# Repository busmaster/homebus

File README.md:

homebus
=======

home automation system

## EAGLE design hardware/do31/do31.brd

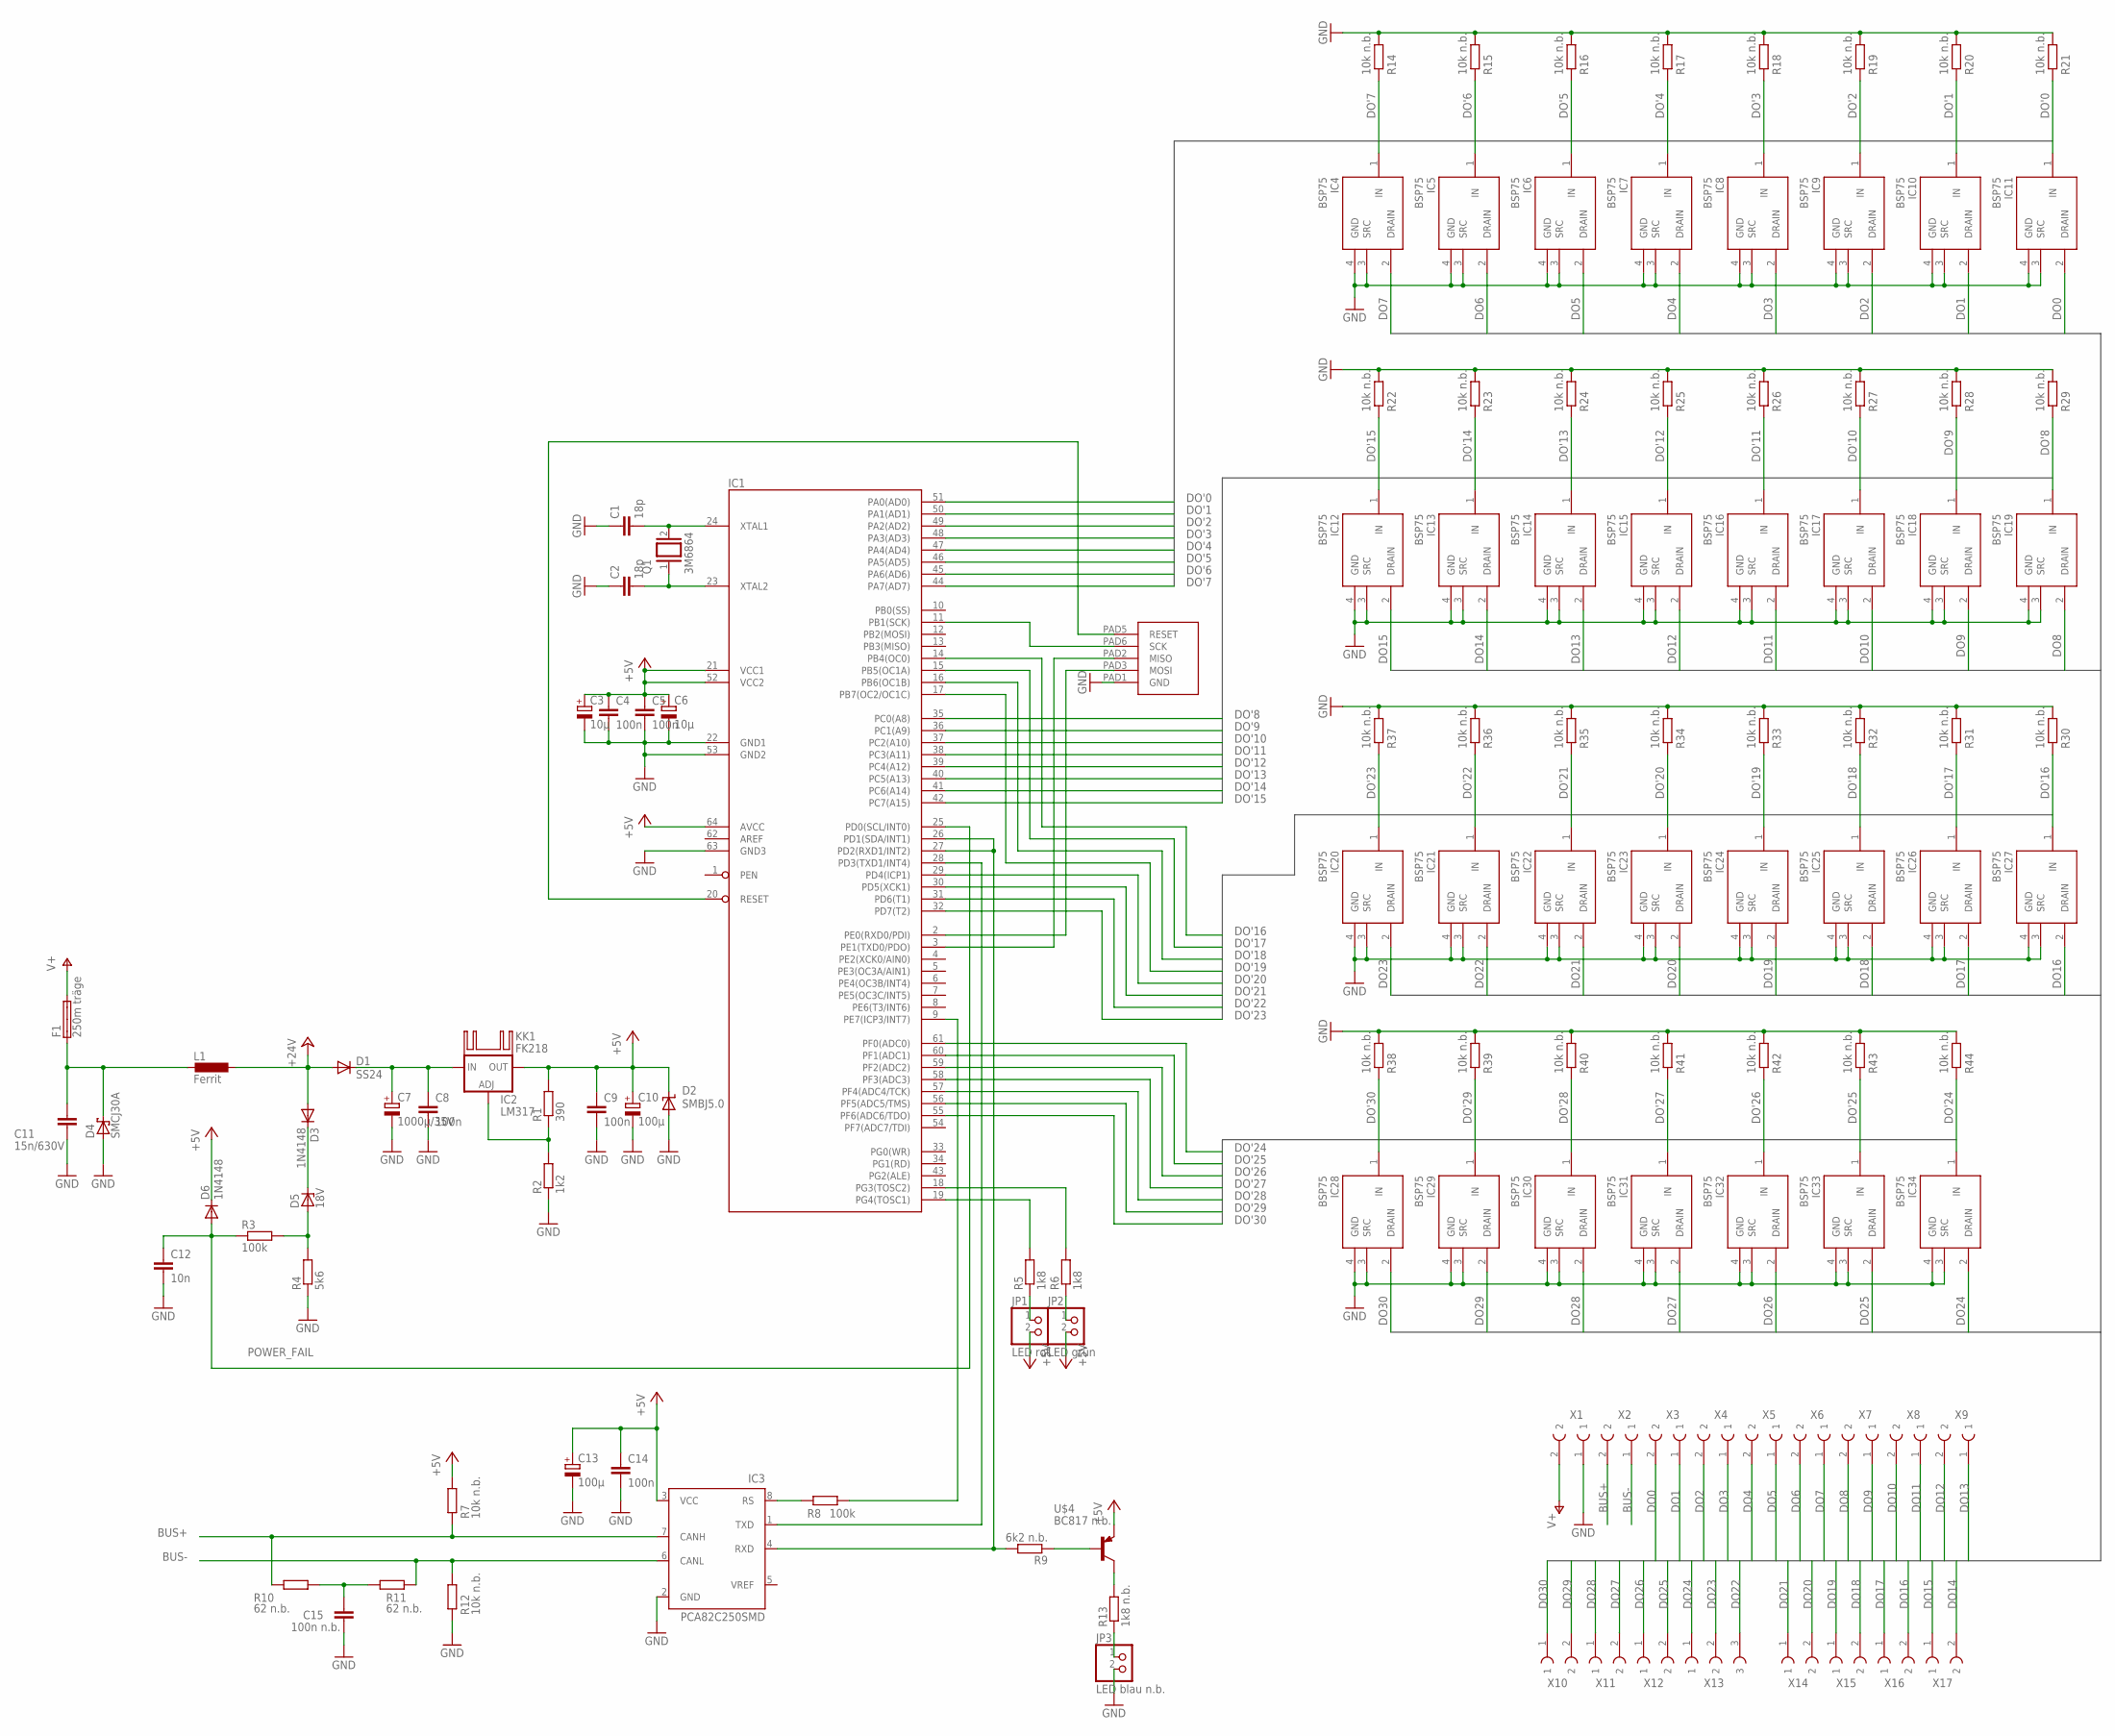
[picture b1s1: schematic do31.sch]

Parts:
C1, C2: 18p; C025-024X044
C3, C6: 10µ; E2-5
C4, C5, C8, C9, C14: 100n; C0603K
C7: 1000µ/35V; E5-13
C10, C13: 100µ; E2,5-5
C11: 15n/630V; C075-042X103
C12: 10n; C0603K
C15: 100n n.b.; C0603K
D1: SS24; SMB
D2: SMBJ5.0; SMBJ
D3, D6: 1N4148; D-2.5
D4: SMCJ30A; SMC
D5: 18V; ZDIO-2.5
F1: 250m träge; SHK20L
IC1: ATMEGA128; TQFP64
IC2: LM317; 317TS
IC3: PCA82C250SMD; SO8
IC4, IC5, IC6, IC7, IC8, IC9, IC10, IC11, IC12, IC13, IC14, IC15, IC16, IC17, IC18, IC19, IC20, IC21, IC22, IC23, IC24, IC25, IC26, IC27, IC28, IC29, IC30, IC31, IC32, IC33, IC34: BSP75; SOT223
JP1: LED rot; 1X02
JP2: LED grün; 1X02
JP3: LED blau n.b.; 1X02
KK1: FK218
L1: Ferrit; L1806
Q1: 3M6864; QS
R1: 390; R0603
R2: 1k2; R0603
R3, R8: 100k; R0603
R4: 5k6; R0603
R5, R6: 1k8; R0603
R7, R12, R14, R15, R16, R17, R18, R19, R20, R21, R22, R23, R24, R25, R26, R27, R28, R29, R30, R31, R32, R33, R34, R35, R36, R37, R38, R39, R40, R41, R42, R43, R44: 10k n.b.; R0603
R9: 6k2 n.b.; R0603
R10, R11: 62 n.b.; R0603
R13: 1k8 n.b.; R0603
U$1: ATMEL_ISP
U$4: BC817 n.b.; SOT323-BEC
X1, X2, X3, X4, X5, X6, X7, X8, X9, X10, X11, X12, X14, X15, X16, X17: AR-KLEMME_508_2POLPTR; W237-2E
X13: AR-KLEMME_508_3POLPTR; W237-3E

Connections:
+5V: C3.+, C4.1, C5.1, C6.+, C9.1, C10.+, C13.+, C14.1, D2.C, D6.C, IC1.21 (VCC1), IC1.52 (VCC2), IC1.64 (AVCC), IC2.2 (OUT), IC3.3 (VCC), JP1.2, JP2.2, R1.2, R7.1, U$4.E
+24V: D1.A, D3.A, L1.1
/RESET: IC1.20 (RESET), U$1.PAD5 (RESET)
AREF: IC1.62 (AREF)
BUS+: IC3.7 (CANH), R7.2, R10.2, X2.2
BUS-: IC3.6 (CANL), R11.1, R12.1, X2.1
DO0: IC11.2 (DRAIN), X3.2
DO1: IC10.2 (DRAIN), X3.1
DO2: IC9.2 (DRAIN), X4.2
DO3: IC8.2 (DRAIN), X4.1
DO4: IC7.2 (DRAIN), X5.2
DO5: IC6.2 (DRAIN), X5.1
DO6: IC5.2 (DRAIN), X6.2
DO7: IC4.2 (DRAIN), X6.1
DO8: IC19.2 (DRAIN), X7.2
DO9: IC18.2 (DRAIN), X7.1
DO10: IC17.2 (DRAIN), X8.2
DO11: IC16.2 (DRAIN), X8.1
DO12: IC15.2 (DRAIN), X9.2
DO13: IC14.2 (DRAIN), X9.1
DO14: IC13.2 (DRAIN), X17.2
DO15: IC12.2 (DRAIN), X17.1
DO16: IC27.2 (DRAIN), X16.2
DO17: IC26.2 (DRAIN), X16.1
DO18: IC25.2 (DRAIN), X15.2
DO19: IC24.2 (DRAIN), X15.1
DO20: IC23.2 (DRAIN), X14.2
DO21: IC22.2 (DRAIN), X14.1
DO22: IC21.2 (DRAIN), X13.3
DO23: IC20.2 (DRAIN), X13.2
DO24: IC34.2 (DRAIN), X13.1
DO25: IC33.2 (DRAIN), X12.2
DO26: IC32.2 (DRAIN), X12.1
DO27: IC31.2 (DRAIN), X11.2
DO28: IC30.2 (DRAIN), X11.1
DO29: IC29.2 (DRAIN), X10.2
DO30: IC28.2 (DRAIN), X10.1
DO'0: IC1.51 (PA0(AD0)), IC11.1 (IN), R21.2
DO'1: IC1.50 (PA1(AD1)), IC10.1 (IN), R20.2
DO'2: IC1.49 (PA2(AD2)), IC9.1 (IN), R19.2
DO'3: IC1.48 (PA3(AD3)), IC8.1 (IN), R18.2
DO'4: IC1.47 (PA4(AD4)), IC7.1 (IN), R17.2
DO'5: IC1.46 (PA5(AD5)), IC6.1 (IN), R16.2
DO'6: IC1.45 (PA6(AD6)), IC5.1 (IN), R15.2
DO'7: IC1.44 (PA7(AD7)), IC4.1 (IN), R14.2
DO'8: IC1.35 (PC0(A8)), IC19.1 (IN), R29.2
DO'9: IC1.36 (PC1(A9)), IC18.1 (IN), R28.2
DO'10: IC1.37 (PC2(A10)), IC17.1 (IN), R27.2
DO'11: IC1.38 (PC3(A11)), IC16.1 (IN), R26.2
DO'12: IC1.39 (PC4(A12)), IC15.1 (IN), R25.2
DO'13: IC1.40 (PC5(A13)), IC14.1 (IN), R24.2
DO'14: IC1.41 (PC6(A14)), IC13.1 (IN), R23.2
DO'15: IC1.42 (PC7(A15)), IC12.1 (IN), R22.2
DO'16: IC1.14 (PB4(OC0)), IC27.1 (IN), R30.2
DO'17: IC1.15 (PB5(OC1A)), IC26.1 (IN), R31.2
DO'18: IC1.16 (PB6(OC1B)), IC25.1 (IN), R32.2
DO'19: IC1.17 (PB7(OC2/OC1C)), IC24.1 (IN), R33.2
DO'20: IC1.29 (PD4(ICP1)), IC23.1 (IN), R34.2
DO'21: IC1.30 (PD5(XCK1)), IC22.1 (IN), R35.2
DO'22: IC1.31 (PD6(T1)), IC21.1 (IN), R36.2
DO'23: IC1.32 (PD7(T2)), IC20.1 (IN), R37.2
DO'24: IC1.61 (PF0(ADC0)), IC34.1 (IN), R44.2
DO'25: IC1.60 (PF1(ADC1)), IC33.1 (IN), R43.2
DO'26: IC1.59 (PF2(ADC2)), IC32.1 (IN), R42.2
DO'27: IC1.58 (PF3(ADC3)), IC31.1 (IN), R41.2
DO'28: IC1.57 (PF4(ADC4/TCK)), IC30.1 (IN), R40.2
DO'29: IC1.56 (PF5(ADC5/TMS)), IC29.1 (IN), R39.2
DO'30: IC1.55 (PF6(ADC6/TDO)), IC28.1 (IN), R38.2
GND: C1.1, C2.1, C3.-, C4.2, C5.2, C6.-, C7.-, C8.2, C9.2, C10.-, C11.2, C12.2, C13.-, C14.2, C15.1, D2.A, D4.A, IC1.22 (GND1), IC1.53 (GND2), IC1.63 (GND3), IC3.2 (GND), IC4.3 (SRC), IC4.4 (GND), IC5.3 (SRC), IC5.4 (GND), IC6.3 (SRC), IC6.4 (GND), IC7.3 (SRC), IC7.4 (GND), IC8.3 (SRC), IC8.4 (GND), IC9.3 (SRC), IC9.4 (GND), IC10.3 (SRC), IC10.4 (GND), IC11.3 (SRC), IC11.4 (GND), IC12.3 (SRC), IC12.4 (GND), IC13.3 (SRC), IC13.4 (GND), IC14.3 (SRC), IC14.4 (GND), IC15.3 (SRC), IC15.4 (GND), IC16.3 (SRC), IC16.4 (GND), IC17.3 (SRC), IC17.4 (GND), IC18.3 (SRC), IC18.4 (GND), IC19.3 (SRC), IC19.4 (GND), IC20.3 (SRC), IC20.4 (GND), IC21.3 (SRC), IC21.4 (GND), IC22.3 (SRC), IC22.4 (GND), IC23.3 (SRC), IC23.4 (GND), IC24.3 (SRC), IC24.4 (GND), IC25.3 (SRC), IC25.4 (GND), IC26.3 (SRC), IC26.4 (GND), IC27.3 (SRC), IC27.4 (GND), IC28.3 (SRC), IC28.4 (GND), IC29.3 (SRC), IC29.4 (GND), IC30.3 (SRC), IC30.4 (GND), IC31.3 (SRC), IC31.4 (GND), IC32.3 (SRC), IC32.4 (GND), IC33.3 (SRC), IC33.4 (GND), IC34.3 (SRC), IC34.4 (GND), JP3.2, R2.1, R4.1, R12.2, R14.1, R15.1, R16.1, R17.1, R18.1, R19.1, R20.1, R21.1, R22.1, R23.1, R24.1, R25.1, R26.1, R27.1, R28.1, R29.1, R30.1, R31.1, R32.1, R33.1, R34.1, R35.1, R36.1, R37.1, R38.1, R39.1, R40.1, R41.1, R42.1, R43.1, R44.1, U$1.PAD1 (GND), X1.1
MISO: IC1.3 (PE1(TXD0/PDO)), U$1.PAD2 (MISO)
MOSI: IC1.2 (PE0(RXD0/PDI)), U$1.PAD3 (MOSI)
unnamed: C11.1, D4.C, F1.1A, L1.2
unnamed: D3.C, D5.C
unnamed: D5.A, R3.2, R4.2
unnamed: C1.2, IC1.24 (XTAL1), Q1.2
unnamed: C2.2, IC1.23 (XTAL2), Q1.1
unnamed: IC3.8 (RS), R8.2
unnamed: IC1.9 (PE7(ICP3/INT7)), R8.1
unnamed: IC2.1 (ADJ), R1.1, R2.2
unnamed: R9.1, U$4.B
unnamed: R13.2, U$4.C
unnamed: C7.+, C8.1, D1.C, IC2.3 (IN)
unnamed: JP3.1, R13.1
unnamed: C15.2, R10.1, R11.2
unnamed: JP1.1, R5.1
unnamed: JP2.1, R6.1
unnamed: IC1.19 (PG4(TOSC1)), R5.2
unnamed: IC1.18 (PG3(TOSC2)), R6.2
POWER_FAIL: C12.1, D6.A, IC1.25 (PD0(SCL/INT0)), R3.1
RXD: IC1.26 (PD1(SDA/INT1)), IC1.27 (PD2(RXD1/INT2)), IC3.4 (RXD), R9.2
SCK: IC1.11 (PB1(SCK)), U$1.PAD6 (SCK)
TXD: IC1.28 (PD3(TXD1/INT4)), IC3.1 (TXD)
V+: F1.2A, X1.2

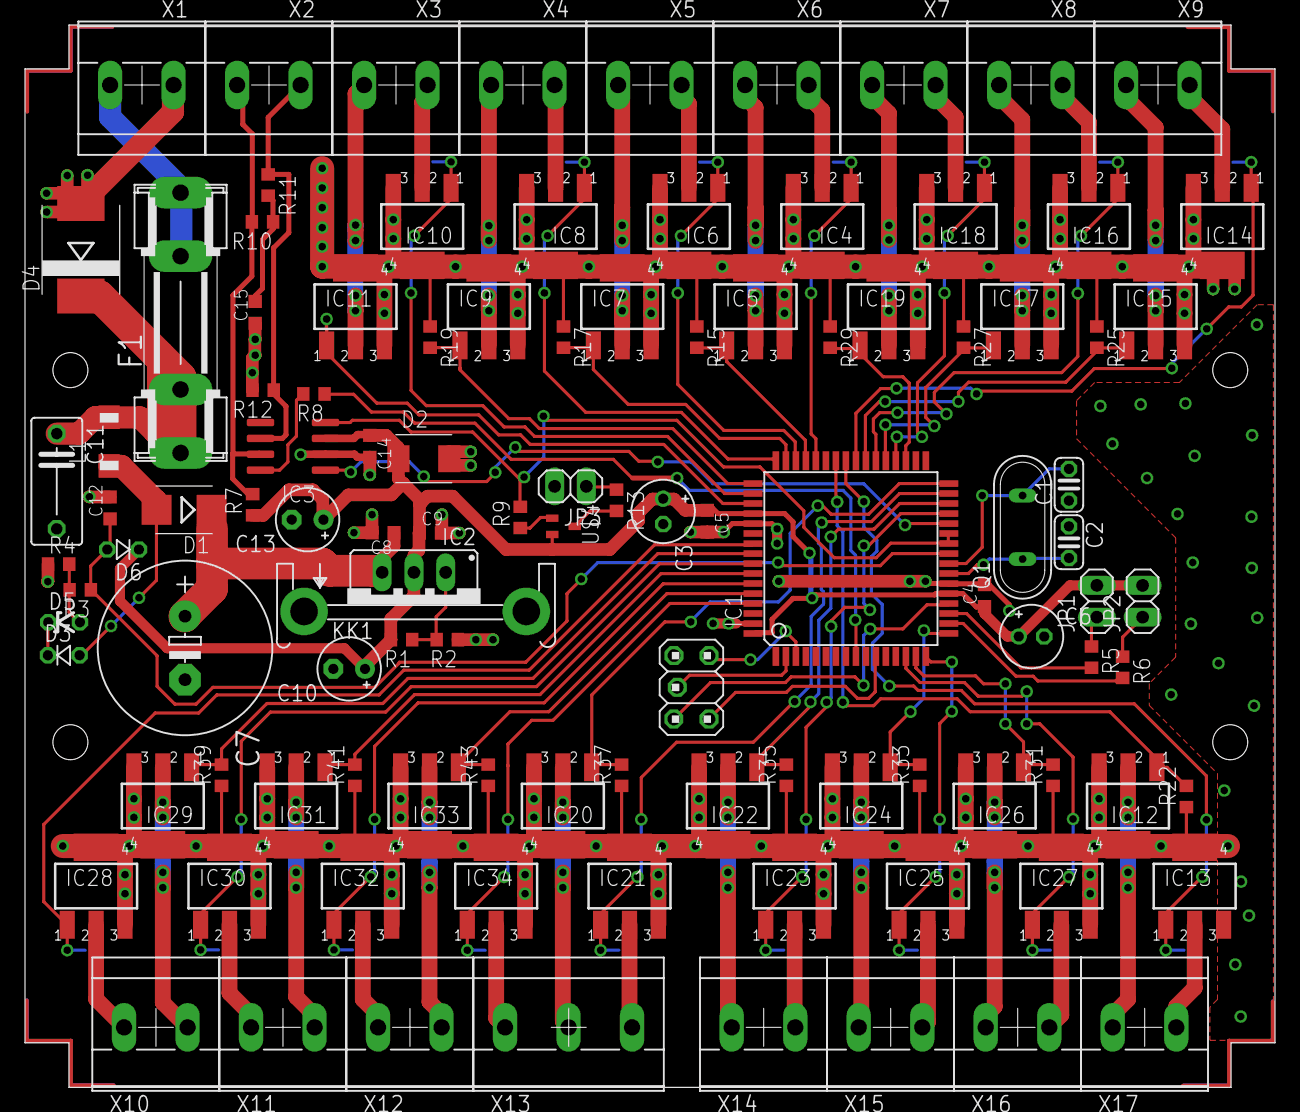
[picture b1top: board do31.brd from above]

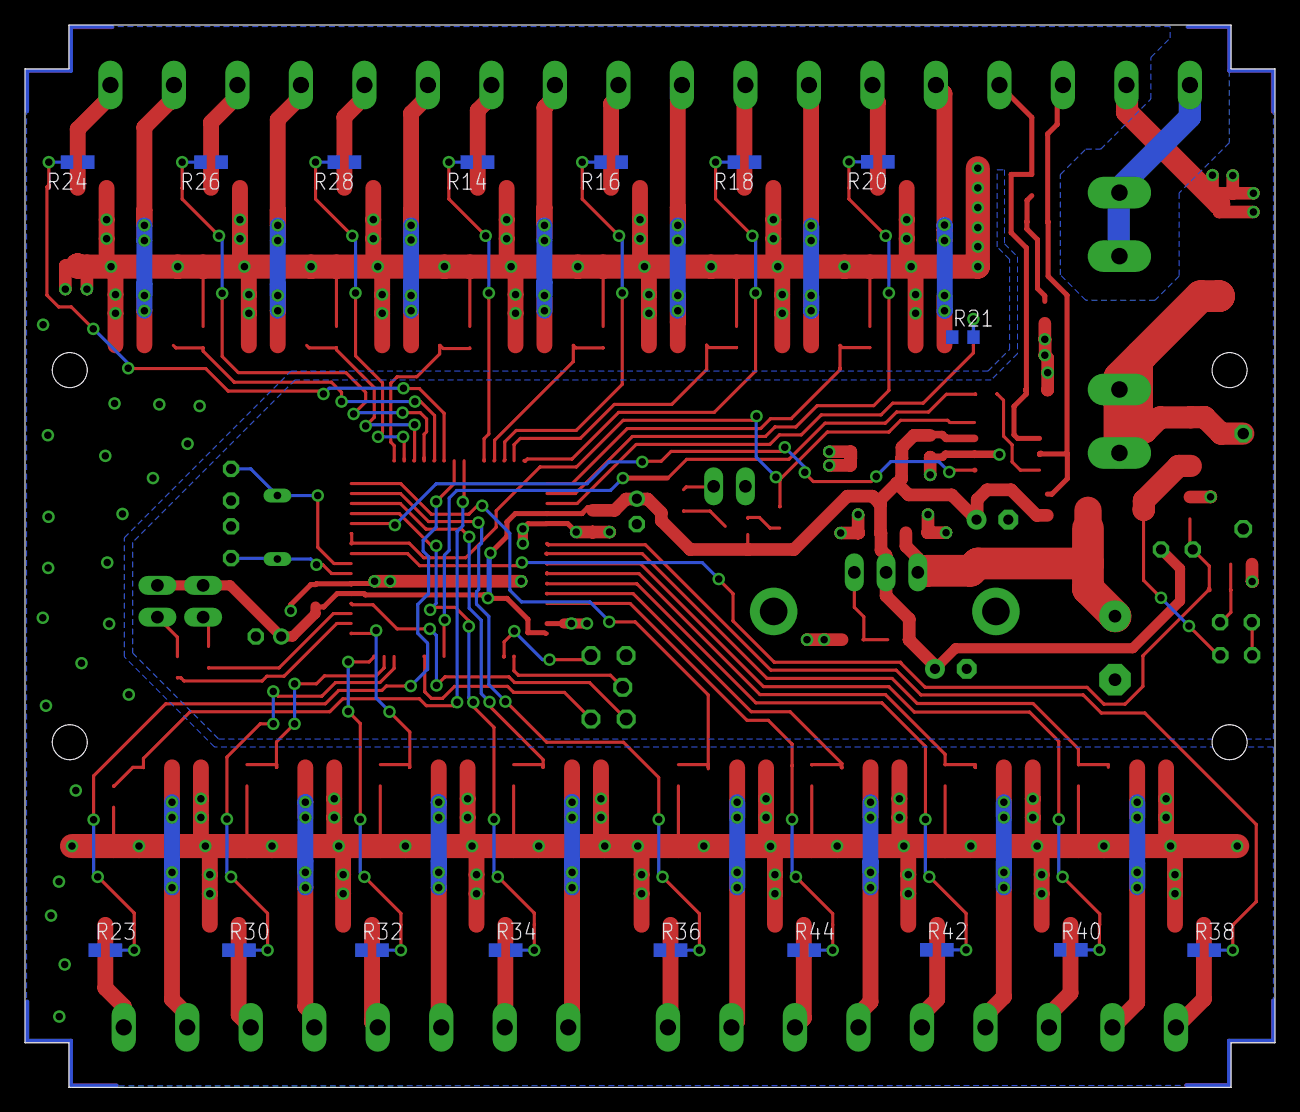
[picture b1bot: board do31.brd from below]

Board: 2 copper layers, 100.0 x 85.0 mm, 126 parts (17 on the bottom side), 92 nets.

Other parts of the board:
U$3: GEHÄUSE_MR6

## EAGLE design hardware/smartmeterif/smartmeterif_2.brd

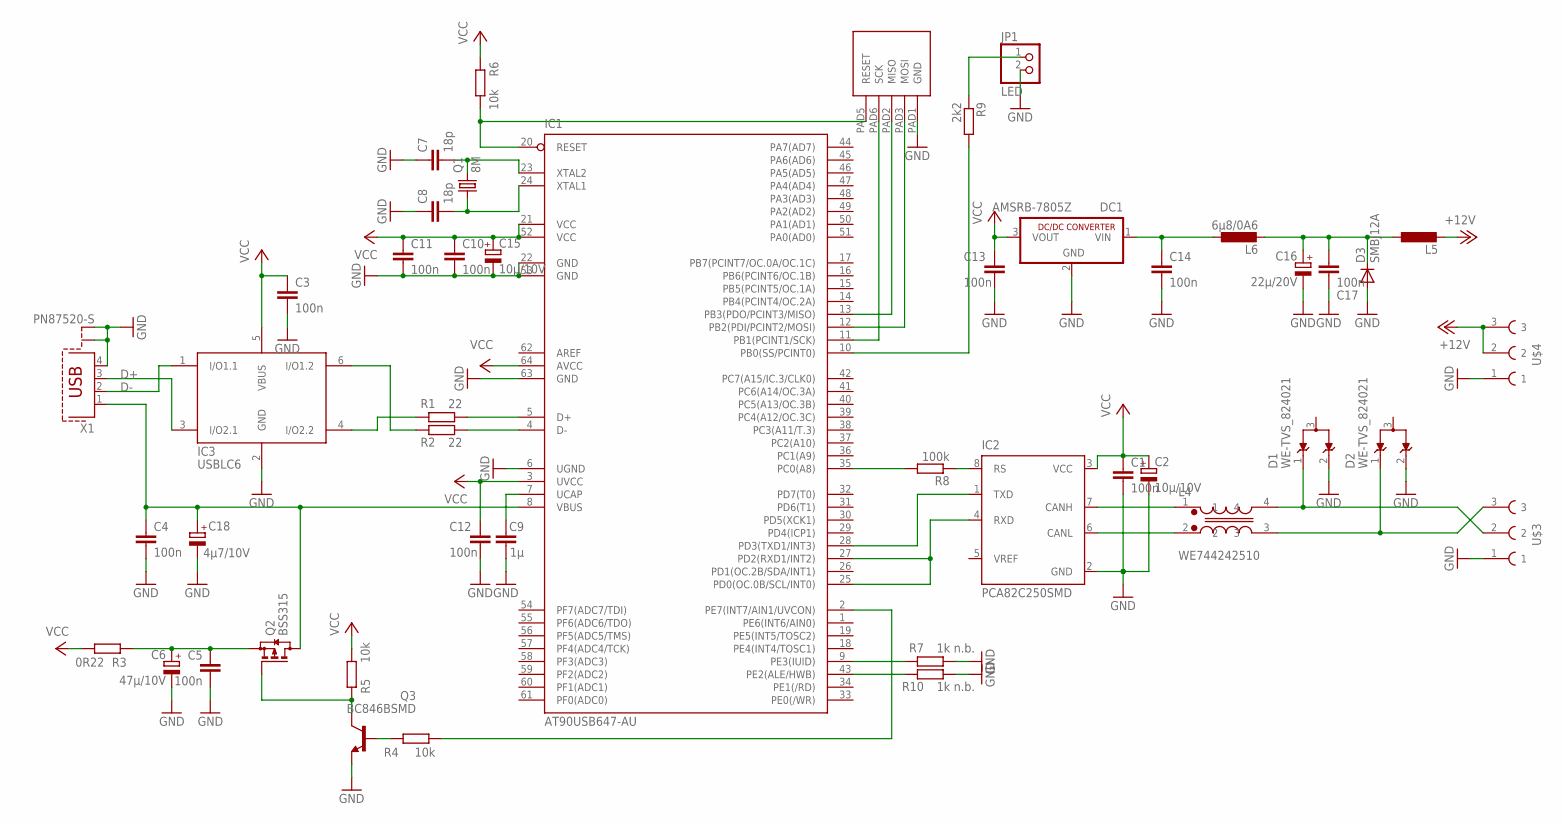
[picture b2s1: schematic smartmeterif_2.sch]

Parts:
C1, C3, C4, C5, C10, C11, C12, C13, C14, C17: 100n; C0603
C2, C15: 10µ/10V; A/3216-18W
C6: 47µ/10V; SMC_C
C7, C8: 18p; C0603
C9: 1µ; C1210K
C16: 22µ/20V; SMC_C
C18: 4µ7/10V; SMC_A
D1, D2: WE-TVS_824021; WE-TVS_SOT23-3L
D3: SMBJ12A; SMB
DC1: AMSRB-7805Z; SIP3
IC1: AT90USB647-AU; TQFP64
IC2: PCA82C250SMD; SO8
IC3: USBLC6; SOT23-6L
JP1: LED; 1X02
L4: WE744242510; WE-SLM
L5: L-EUL1806; L1806
L6: 6µ8/0A6; L1812
Q1: 8M; SM49
Q2: BSS315; SOT23
Q3: BC846BSMD; SOT23
R1, R2: 22; R0603
R3: 0R22; R0603
R4, R5, R6: 10k; R0603
R7, R10: 1k n.b.; R0603
R8: 100k; R0603
R9: 2k2; R0603
U$2: ATMEL_ISP
U$3, U$4: MKDSO_2.5/3_L; PHOENIX_MKDSO_2.5/3_L
X1: PN87520-S

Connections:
+12V: L5.2, U$4.2, U$4.3
.D+: IC3.4 (I/O2.2), R1.1
.D-: IC3.6 (I/O1.2), R2.1
B+: D1.1, L4.4, U$3.2
B-: D2.1, L4.3, U$3.3
D+: IC3.3 (I/O2.1), X1.3
D-: IC3.1 (I/O1.1), X1.2
GND: C1.2, C2.-, C3.2, C4.2, C5.2, C6.-, C7.1, C8.1, C9.1, C10.2, C11.2, C12.2, C13.2, C14.2, C15.-, C16.-, C17.2, C18.-, D1.2, D2.2, D3.A, DC1.2 (GND), IC1.6 (UGND), IC1.22 (GND), IC1.53 (GND), IC1.63 (GND), IC2.2 (GND), IC3.2 (GND), JP1.2, Q3.2 (E), R7.2, R10.2, U$2.PAD1 (GND), U$3.1, U$4.1, X1.4, X1.S1, X1.S2
unnamed: IC1.5 (D+), R1.2
unnamed: IC1.4 (D-), R2.2
unnamed: C4.1, C18.+, IC1.8 (VBUS), Q2.3 (D), X1.1
unnamed: C5.1, C6.+, Q2.2 (S), R3.1
unnamed: IC1.2 (PE7(INT7/AIN1/UVCON)), R4.2
unnamed: IC2.7 (CANH), L4.1
unnamed: Q2.1 (G), Q3.3 (C), R5.1
unnamed: Q3.1 (B), R4.1
unnamed: IC1.10 (PB0(SS/PCINT0)), R9.2
unnamed: JP1.1, R9.1
unnamed: IC1.35 (PC0(A8)), R8.2
unnamed: IC1.28 (PD3(TXD1/INT3)), IC2.1 (TXD)
unnamed: IC2.6 (CANL), L4.2
unnamed: IC1.25 (PD0(OC.0B/SCL/INT0)), IC1.27 (PD2(RXD1/INT2)), IC2.4 (RXD)
unnamed: IC1.43 (PE2(ALE/HWB)), R10.1
unnamed: IC1.20 (RESET), R6.2, U$2.PAD5 (RESET)
unnamed: IC1.11 (PB1(PCINT1/SCK)), U$2.PAD6 (SCK)
unnamed: IC1.12 (PB2(PDI/PCINT2/MOSI)), U$2.PAD3 (MOSI)
unnamed: IC1.13 (PB3(PDO/PCINT3/MISO)), U$2.PAD2 (MISO)
unnamed: C7.2, IC1.23 (XTAL2), Q1.2
unnamed: C8.2, IC1.24 (XTAL1), Q1.1
unnamed: C9.2, IC1.7 (UCAP)
unnamed: IC2.8 (RS), R8.1
unnamed: C16.+, C17.1, D3.C, L5.1, L6.2
unnamed: C14.1, DC1.1 (VIN), L6.1
unnamed: IC1.9 (PE3(IUID)), R7.1
VCC: C1.1, C2.+, C3.1, C10.1, C11.1, C12.1, C13.1, C15.+, DC1.3 (VOUT), IC1.3 (UVCC), IC1.21 (VCC), IC1.52 (VCC), IC1.64 (AVCC), IC2.3 (VCC), IC3.5 (VBUS), R3.2, R5.2, R6.1

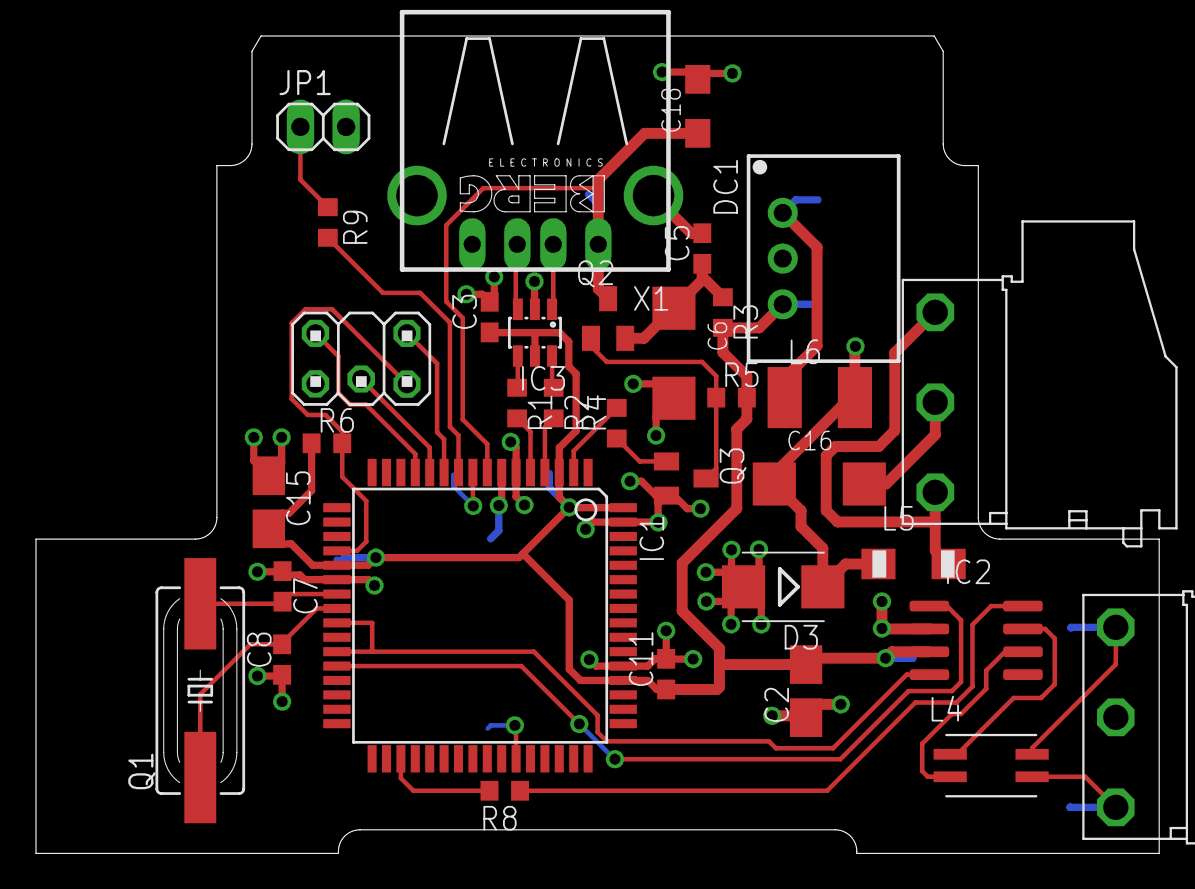
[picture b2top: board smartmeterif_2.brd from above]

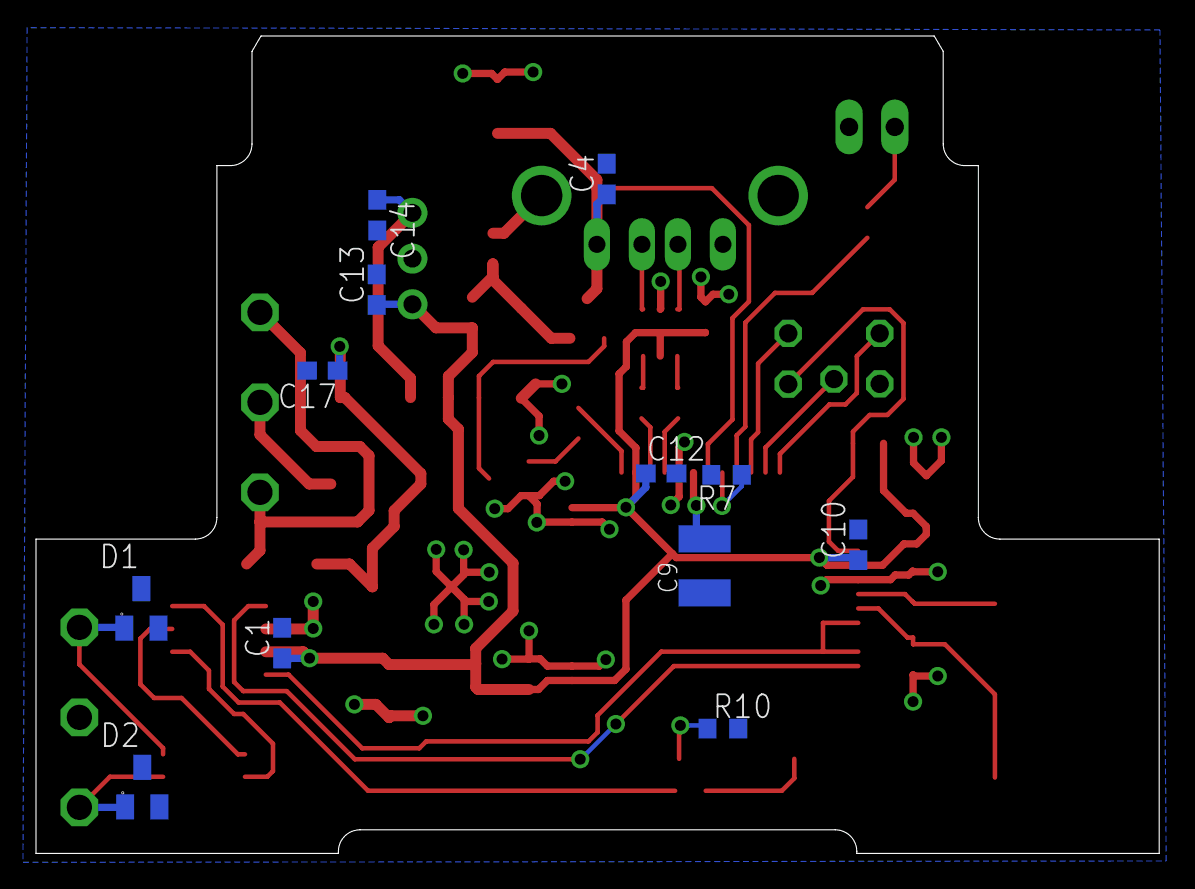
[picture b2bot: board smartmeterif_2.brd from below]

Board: 2 copper layers, 62.4 x 45.4 mm, 47 parts (12 on the bottom side), 35 nets.

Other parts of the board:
U$5: GEHÄUSE_PHOENIX_BC_17.8_REDUCED_REDUCED

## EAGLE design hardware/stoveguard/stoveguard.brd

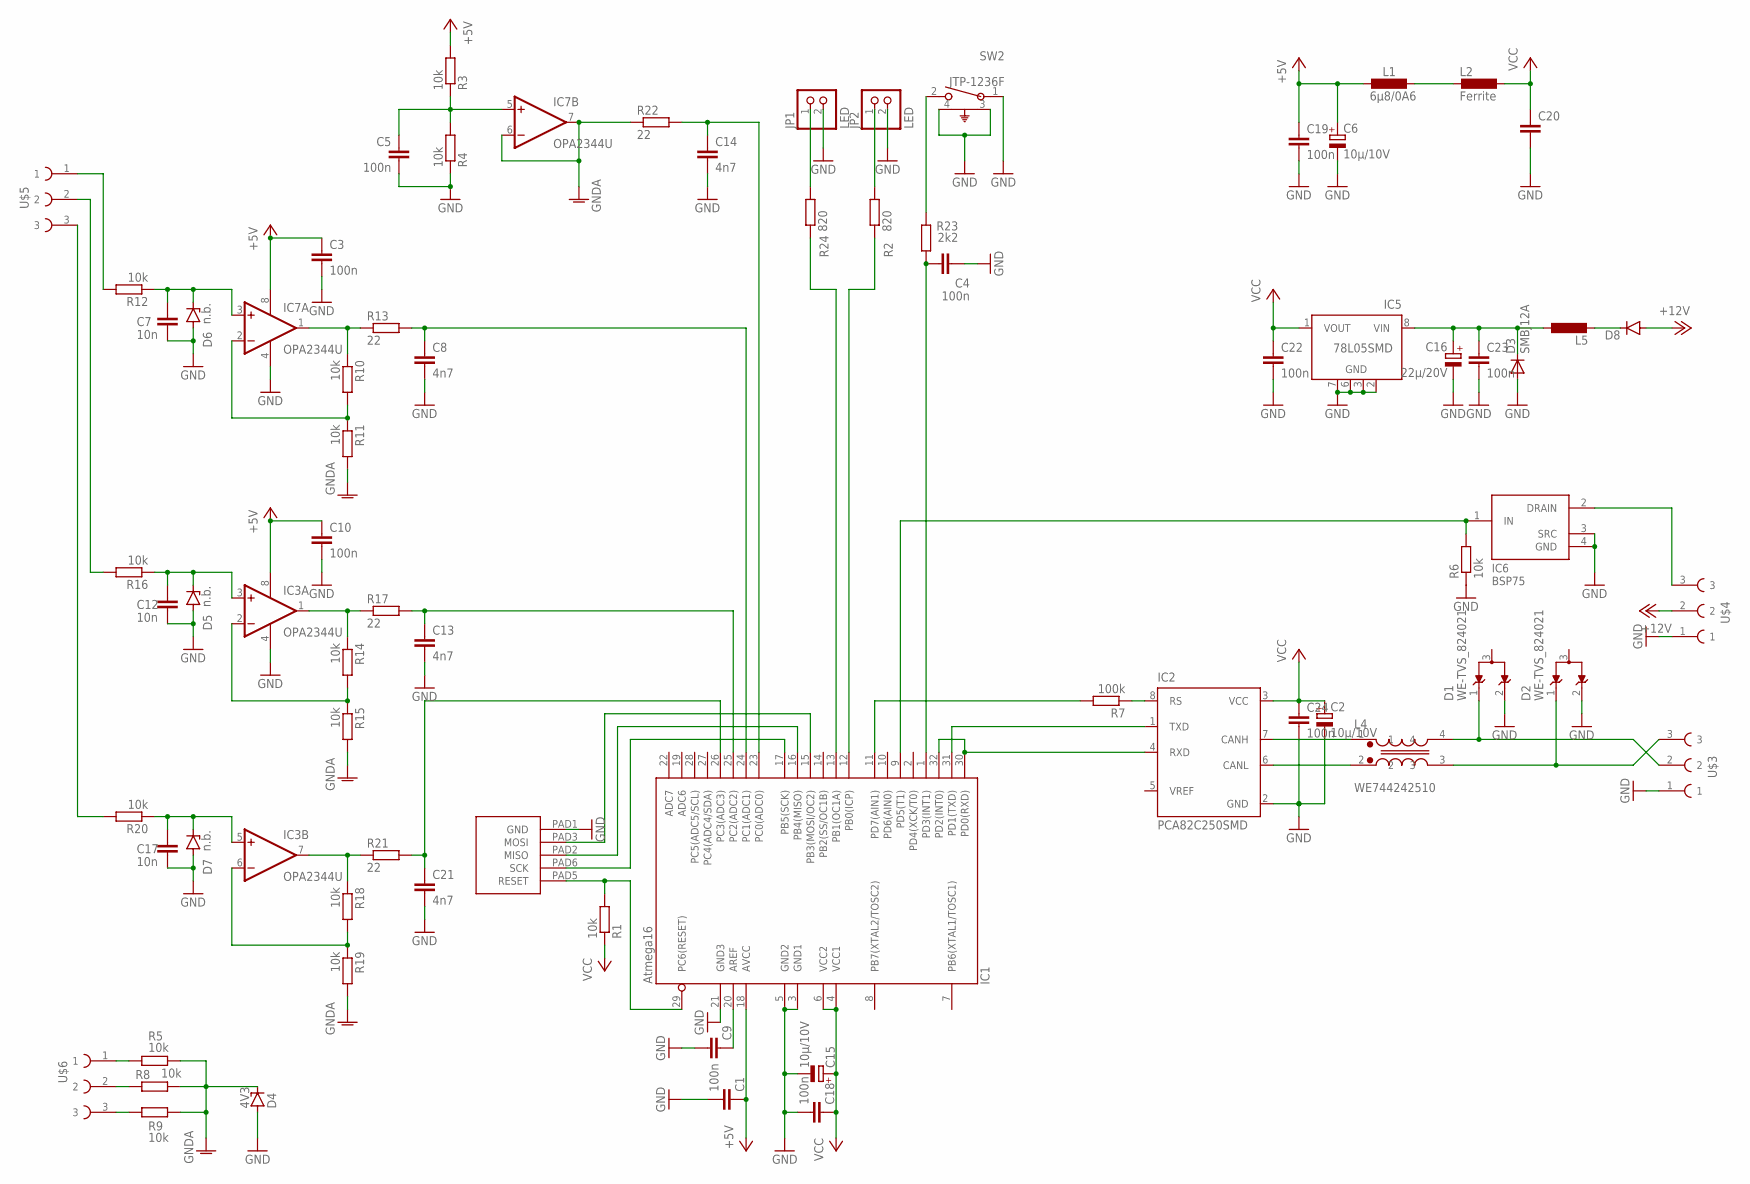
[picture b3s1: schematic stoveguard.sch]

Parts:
C1, C3, C4, C5, C10, C18, C19, C22, C23, C24: 100n; C0603
C2, C6, C15: 10µ/10V; A/3216-18W
C7, C12, C17: 10n; C0603
C8, C13, C14, C21: 4n7; C0603
C9: CC1206; C1206
C16: 22µ/20V; SMC_C
C20: CC0603; C0603
D1, D2: WE-TVS_824021; WE-TVS_SOT23-3L
D3: SMBJ12A; SMB
D4: 4V3; SOD80C
D5, D6, D7: n.b.; SOD80C
D8: DIODE-MINIMELF; MINIMELF
IC1: Atmega16; TQFP32-08
IC2: PCA82C250SMD; SO8
IC3, IC7: OPA2344U; SO08
IC5: 78L05SMD; SO08
IC6: BSP75; SOT223
JP1, JP2: LED; 1X02
L1: 6µ8/0A6; L1812
L2: Ferrite; L1806
L4: WE744242510; WE-SLM
L5: L-EUL1806; L1806
R1, R3, R4, R5, R6, R8, R9, R10, R11, R12, R14, R15, R16, R18, R19, R20: 10k; R0603
R2, R24: 820; R0603
R7: 100k; R0603
R13, R17, R21, R22: 22; R0603
R23: 2k2; R0603
SW2: JTP-1236F; SW2_1825027-E
U$2: ATMEL_ISP
U$3, U$4: MKDSO_2.5/3_L; PHOENIX_MKDSO_2.5/3_L
U$5, U$6: MKDSO_2.5/3_R; PHOENIX_MKDSO_2.5/3_R

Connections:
+5V: C1.1, C3.1, C6.+, C10.1, C19.1, IC1.18 (AVCC), IC3.8 (V+), IC7.8 (V+), L1.2, R3.2
+12V: D8.A, U$4.2
B+: D1.1, L4.4, U$3.2
B-: D2.1, L4.3, U$3.3
GND: C1.2, C2.-, C3.2, C4.1, C5.2, C6.-, C7.2, C8.2, C9.2, C10.2, C12.2, C13.2, C14.2, C15.-, C16.-, C17.2, C18.2, C19.2, C20.2, C21.2, C22.2, C23.2, C24.2, D1.2, D2.2, D3.A, D4.A, D5.A, D6.A, D7.A, IC1.3 (GND1), IC1.5 (GND2), IC1.21 (GND3), IC2.2 (GND), IC3.4 (V-), IC5.2 (GND), IC5.3 (GND), IC5.6 (GND), IC5.7 (GND), IC6.3 (SRC), IC6.4 (GND), IC7.4 (V-), JP1.2, JP2.2, R4.1, R6.1, SW2.1, SW2.3, SW2.4, U$2.PAD1 (GND), U$3.1, U$4.1
GNDA: D4.C, IC7.6 (-IN), IC7.7 (OUT), R5.1, R8.1, R9.1, R11.2, R15.2, R19.2, R22.1
unnamed: L1.1, L2.2
unnamed: IC6.2 (DRAIN), U$4.3
unnamed: C9.1, IC1.20 (AREF)
unnamed: IC1.15 (PB3(MOSI/OC2)), U$2.PAD3 (MOSI)
unnamed: IC1.16 (PB4(MISO)), U$2.PAD2 (MISO)
unnamed: IC1.17 (PB5(SCK)), U$2.PAD6 (SCK)
unnamed: IC1.9 (PD5(T1)), IC6.1 (IN), R6.2
unnamed: R5.2, U$6.1
unnamed: C5.1, IC7.5 (+IN), R3.1, R4.2
unnamed: IC2.7 (CANH), L4.1
unnamed: R8.2, U$6.2
unnamed: R9.2, U$6.3
unnamed: JP1.1, R24.2
unnamed: IC1.12 (PB0(ICP)), R2.1
unnamed: IC1.11 (PD7(AIN1)), R7.2
unnamed: IC1.31 (PD1(TXD)), IC2.1 (TXD)
unnamed: IC2.6 (CANL), L4.2
unnamed: IC1.30 (PD0(RXD)), IC1.32 (PD2(INT0)), IC2.4 (RXD)
unnamed: R12.2, U$5.1
unnamed: IC1.29 (PC6(RESET)), R1.2, U$2.PAD5 (RESET)
unnamed: C7.1, D6.C, IC7.3 (+IN), R12.1
unnamed: IC7.2 (-IN), R10.2, R11.1
unnamed: IC7.1 (OUT), R10.1, R13.1
unnamed: C4.2, IC1.1 (PD3(INT1)), R23.2
unnamed: R23.1, SW2.2
unnamed: C8.1, IC1.24 (PC1(ADC1)), R13.2
unnamed: IC2.8 (RS), R7.1
unnamed: C16.+, C23.1, D3.C, IC5.8 (VIN), L5.1
unnamed: C12.1, D5.C, IC3.3 (+IN), R16.1
unnamed: IC3.2 (-IN), R14.2, R15.1
unnamed: IC3.1 (OUT), R14.1, R17.1
unnamed: C13.1, IC1.25 (PC2(ADC2)), R17.2
unnamed: R16.2, U$5.2
unnamed: C17.1, D7.C, IC3.5 (+IN), R20.1
unnamed: IC3.6 (-IN), R18.2, R19.1
unnamed: IC3.7 (OUT), R18.1, R21.1
unnamed: C21.1, IC1.26 (PC3(ADC3)), R21.2
unnamed: R20.2, U$5.3
unnamed: C14.1, IC1.23 (PC0(ADC0)), R22.2
unnamed: D8.C, L5.2
unnamed: IC1.13 (PB1(OC1A)), R24.1
unnamed: JP2.1, R2.2
VCC: C2.+, C15.+, C18.1, C20.1, C22.1, C24.1, IC1.4 (VCC1), IC1.6 (VCC2), IC2.3 (VCC), IC5.1 (VOUT), L2.1, R1.1

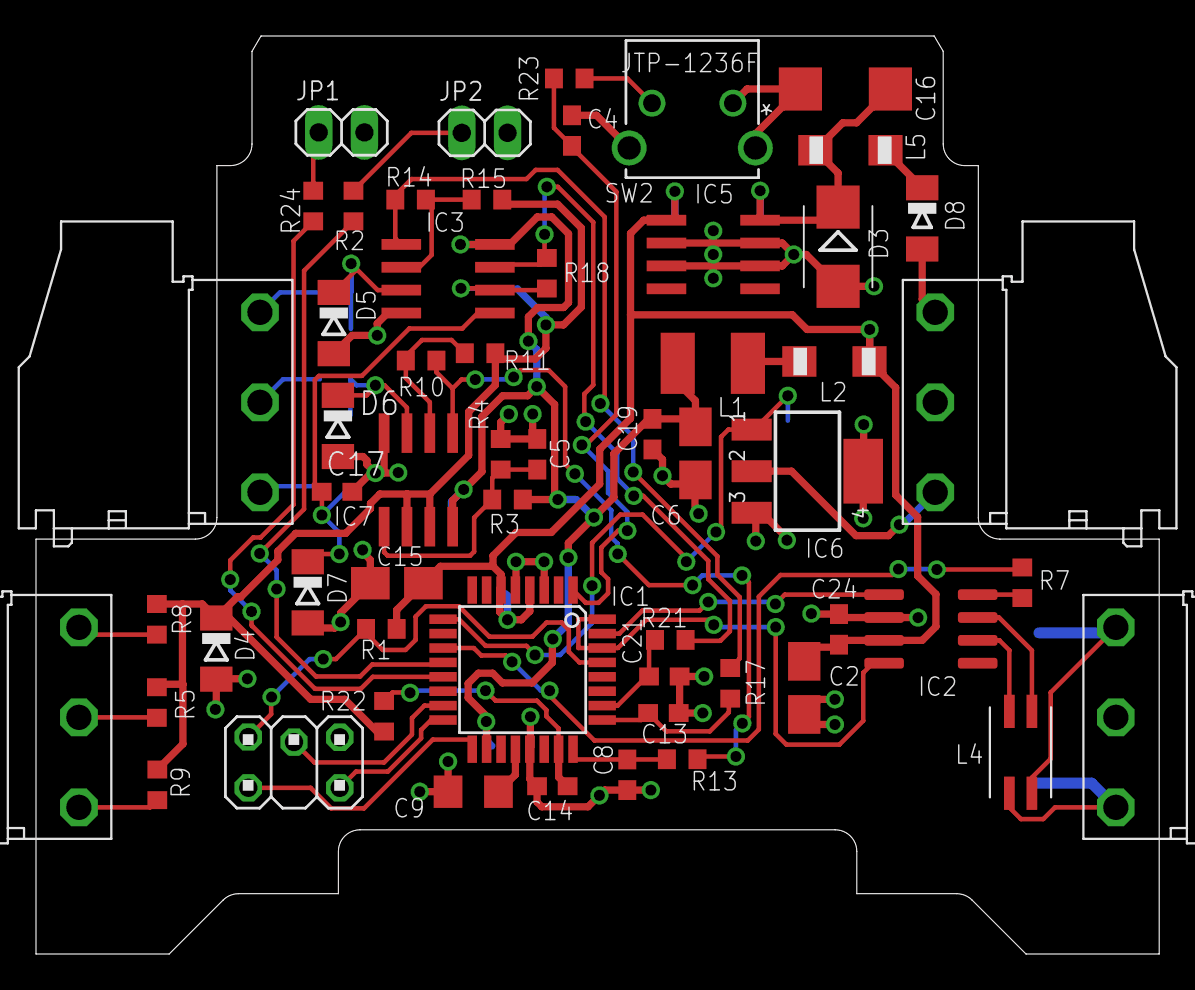
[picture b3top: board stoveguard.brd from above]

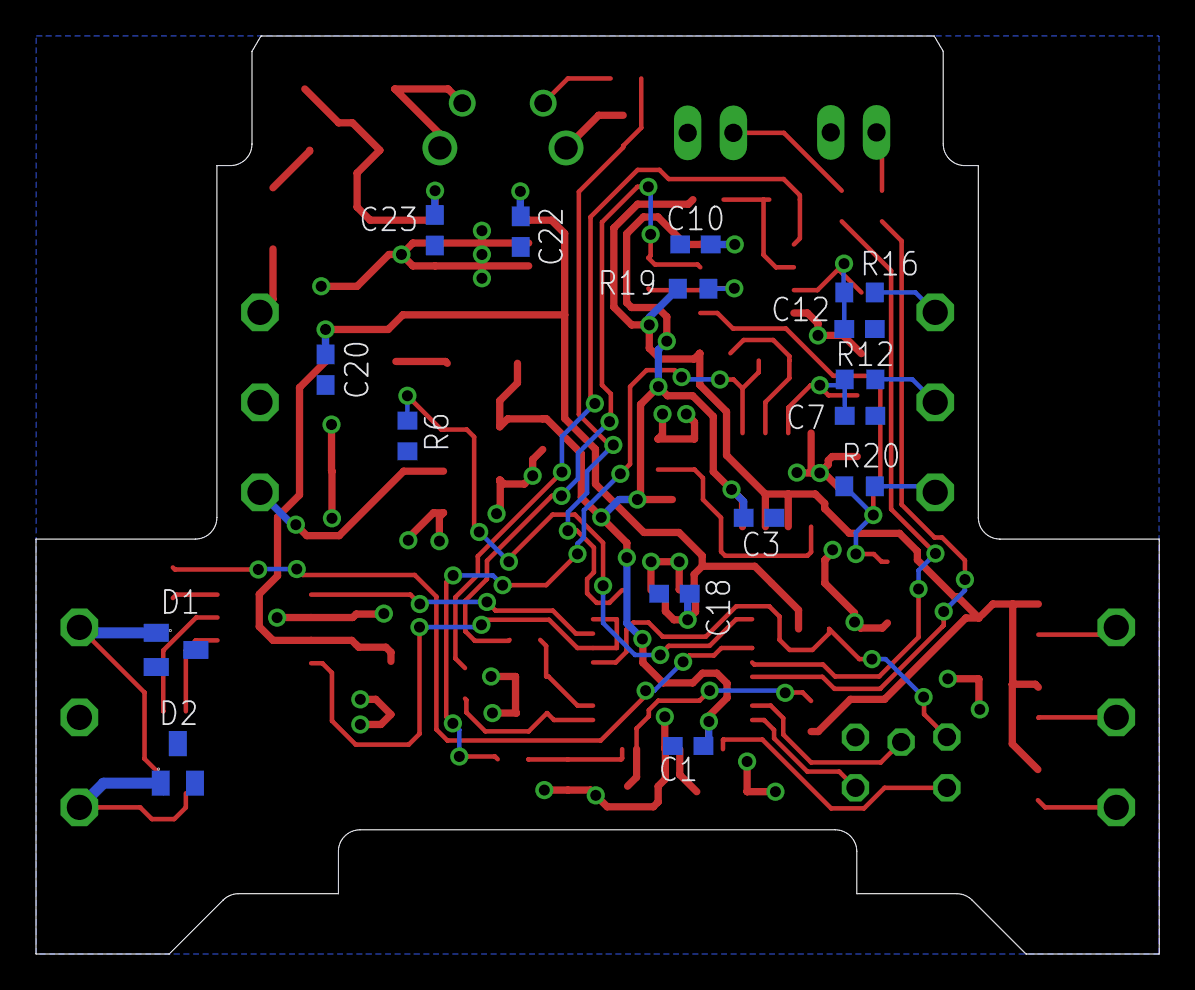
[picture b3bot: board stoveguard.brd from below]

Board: 2 copper layers, 62.4 x 51.0 mm, 74 parts (16 on the bottom side), 49 nets.

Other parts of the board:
U$7: GEHÄUSE_PHOENIX_BC_17.8_REDUCED

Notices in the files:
parts and their libraries:
EagleLibrary_Wuerth_Elektronik_eiSos_V6_: Copyright: Würth Elektronik
COPYRIGHT: Copyright (C) 2016 Accelerated Designs. All rights reserved
